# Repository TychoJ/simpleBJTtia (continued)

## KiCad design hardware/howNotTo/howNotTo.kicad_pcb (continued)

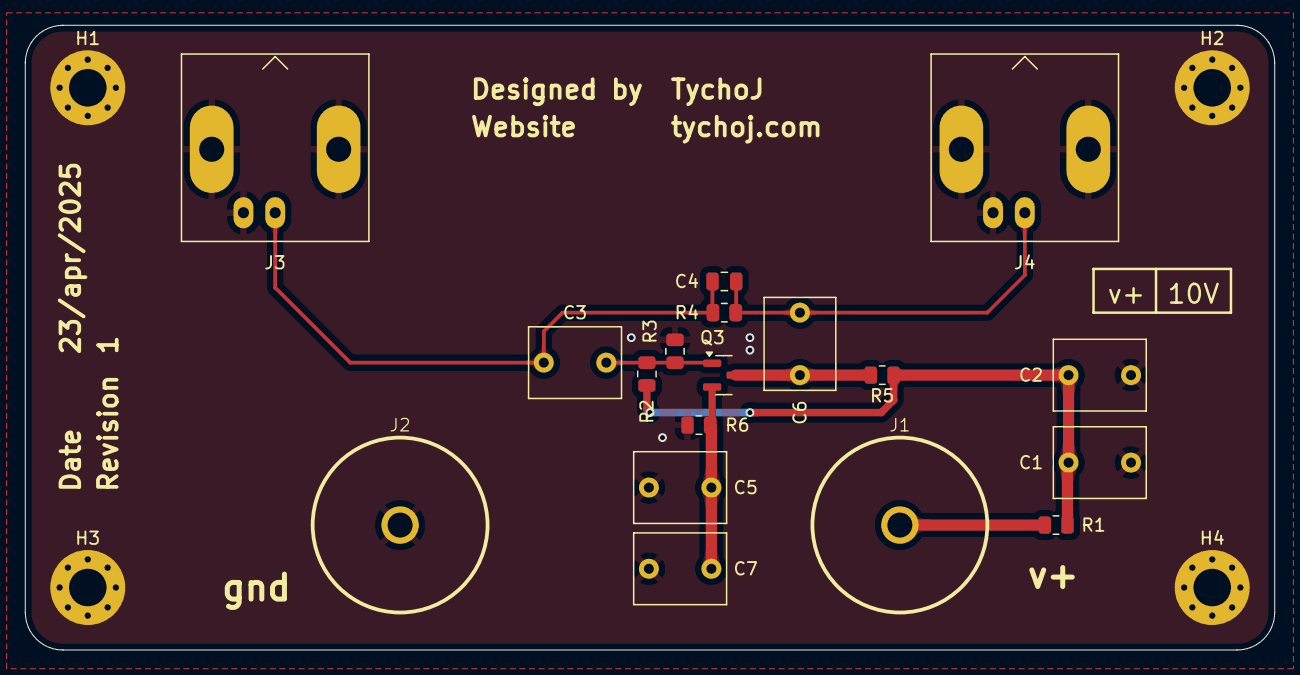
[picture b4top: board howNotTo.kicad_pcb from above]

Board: 2 copper layers, 100.0 x 50.0 mm, 22 parts (0 on the bottom side), 8 nets.

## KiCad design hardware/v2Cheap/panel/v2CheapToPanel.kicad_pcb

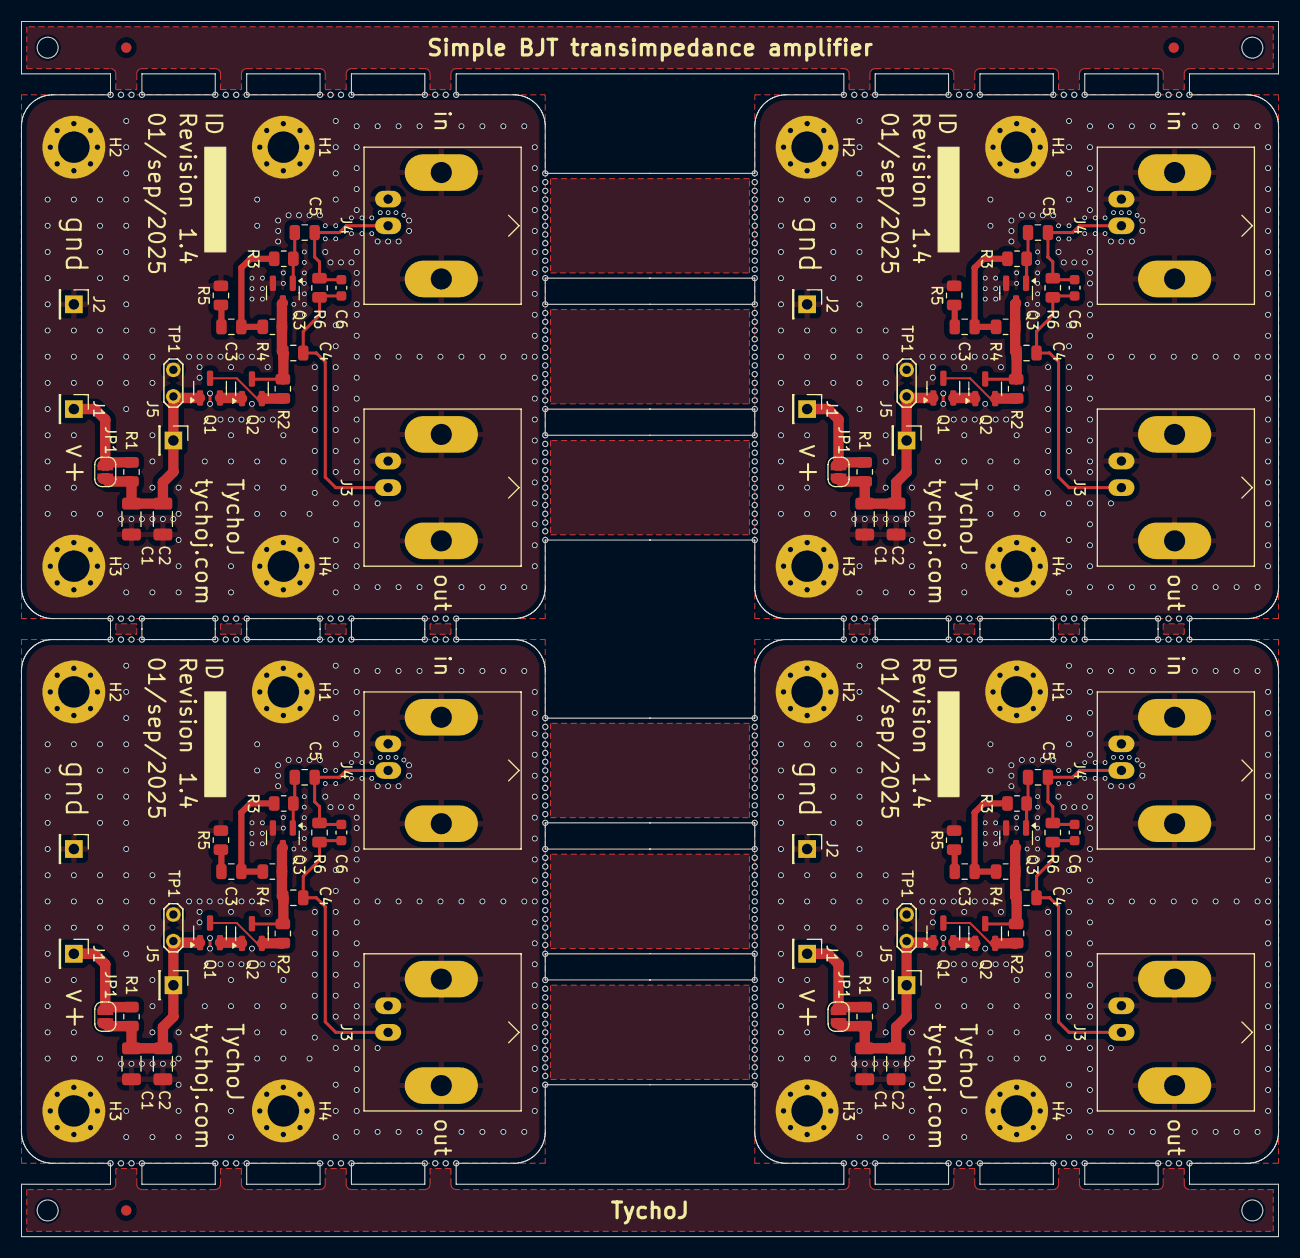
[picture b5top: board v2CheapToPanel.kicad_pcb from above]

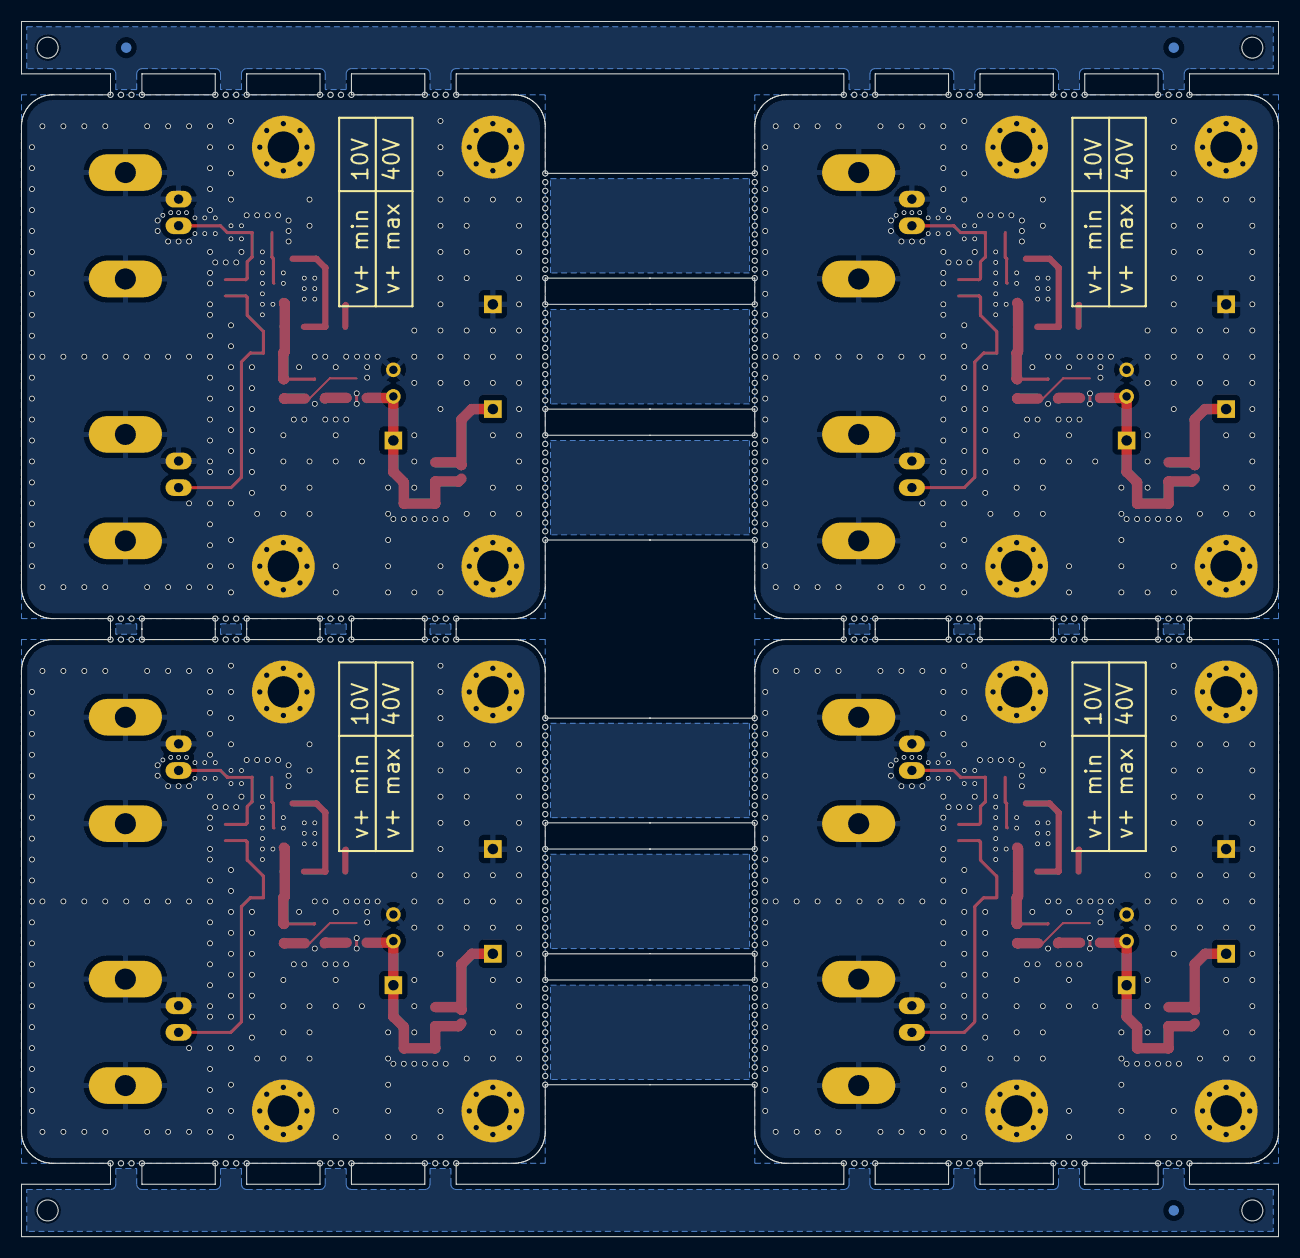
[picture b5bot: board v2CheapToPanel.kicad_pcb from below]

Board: 2 copper layers, 120.0 x 116.0 mm, 398 parts (3 on the bottom side), 44 nets.

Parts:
C1, C1#2, C1#3, C1#4, C2, C2#2, C2#3, C2#4: 4u7; C_1206_3216Metric
C3, C3#2, C3#3, C3#4: 10n; C_0805_2012Metric
C4, C4#2, C4#3, C4#4, C5, C5#2, C5#3, C5#4: 1u; C_0805_2012Metric
C6, C6#2, C6#3, C6#4: TBD; C_0603_1608Metric
H1, H1#2, H1#3, H1#4, H2, H2#2, H2#3, H2#4, H3, H3#2, H3#3, H3#4, H4, H4#2, H4#3, H4#4: MountingHole_Pad_MP; MountingHole_3mm_Pad_Via
J1, J1#2, J1#3, J1#4: +10V; PinHeader_1x01_P2.54mm_Vertical
J2, J2#2, J2#3, J2#4: GND; PinHeader_1x01_P2.54mm_Vertical
J3, J3#2, J3#3, J3#4, J4, J4#2, J4#3, J4#4: Conn_Coaxial; BNC_Amphenol_B6252HB-NPP3G-50_Horizontal
J5, J5#2, J5#3, J5#4: Conn_01x01_Pin; PinHeader_1x01_P2.54mm_Vertical
JP1, JP1#2, JP1#3, JP1#4: SolderJumper_2_Open; SolderJumper-2_P1.3mm_Open_RoundedPad1.0x1.5mm
KiKit_FID_B_1, KiKit_FID_B_2, KiKit_FID_B_3: Fiducial
KiKit_FID_T_1, KiKit_FID_T_2, KiKit_FID_T_3: Fiducial
KiKit_MB_1_1, KiKit_MB_1_2, KiKit_MB_1_3, KiKit_MB_1_4, KiKit_MB_1_5, KiKit_MB_1_6, KiKit_MB_1_7, KiKit_MB_1_8, KiKit_MB_1_9, KiKit_MB_1_10, KiKit_MB_1_11, KiKit_MB_1_12, KiKit_MB_1_13, KiKit_MB_2_1, KiKit_MB_2_2, KiKit_MB_2_3, KiKit_MB_2_4, KiKit_MB_2_5, KiKit_MB_2_6, KiKit_MB_2_7, KiKit_MB_2_8, KiKit_MB_2_9, KiKit_MB_2_10, KiKit_MB_2_11, KiKit_MB_2_12, KiKit_MB_2_13, KiKit_MB_3_1, KiKit_MB_3_2, KiKit_MB_3_3, KiKit_MB_3_4, KiKit_MB_3_5, KiKit_MB_3_6, KiKit_MB_3_7, KiKit_MB_3_8, KiKit_MB_3_9, KiKit_MB_3_10, KiKit_MB_3_11, KiKit_MB_3_12, KiKit_MB_3_13, KiKit_MB_4_1, KiKit_MB_4_2, KiKit_MB_4_3, KiKit_MB_4_4, KiKit_MB_5_1, KiKit_MB_5_2, KiKit_MB_5_3, KiKit_MB_5_4, KiKit_MB_6_1, KiKit_MB_6_2, KiKit_MB_6_3, KiKit_MB_6_4, KiKit_MB_7_1, KiKit_MB_7_2, KiKit_MB_7_3, KiKit_MB_7_4, KiKit_MB_8_1, KiKit_MB_8_2, KiKit_MB_8_3, KiKit_MB_8_4, KiKit_MB_9_1, KiKit_MB_9_2, KiKit_MB_9_3, KiKit_MB_9_4, KiKit_MB_10_1, KiKit_MB_10_2, KiKit_MB_10_3, KiKit_MB_10_4, KiKit_MB_11_1, KiKit_MB_11_2, KiKit_MB_11_3, KiKit_MB_11_4, KiKit_MB_12_1, KiKit_MB_12_2, KiKit_MB_12_3, KiKit_MB_12_4, KiKit_MB_12_5, KiKit_MB_12_6, KiKit_MB_12_7, KiKit_MB_12_8, KiKit_MB_12_9, KiKit_MB_12_10, KiKit_MB_12_11, KiKit_MB_12_12, KiKit_MB_12_13, KiKit_MB_13_1, KiKit_MB_13_2, KiKit_MB_13_3, KiKit_MB_13_4, KiKit_MB_13_5, KiKit_MB_13_6, KiKit_MB_13_7, KiKit_MB_13_8, KiKit_MB_13_9, KiKit_MB_13_10, KiKit_MB_13_11, KiKit_MB_13_12, KiKit_MB_13_13, KiKit_MB_14_1, KiKit_MB_14_2, KiKit_MB_14_3, KiKit_MB_14_4, KiKit_MB_14_5, KiKit_MB_14_6, KiKit_MB_14_7, KiKit_MB_14_8, KiKit_MB_14_9, KiKit_MB_14_10, KiKit_MB_14_11, KiKit_MB_14_12, KiKit_MB_14_13, KiKit_MB_15_1, KiKit_MB_15_2, KiKit_MB_15_3, KiKit_MB_15_4, KiKit_MB_16_1, KiKit_MB_16_2, KiKit_MB_16_3, KiKit_MB_16_4, KiKit_MB_17_1, KiKit_MB_17_2, KiKit_MB_17_3, KiKit_MB_17_4, KiKit_MB_18_1, KiKit_MB_18_2, KiKit_MB_18_3, KiKit_MB_18_4, KiKit_MB_19_1, KiKit_MB_19_2, KiKit_MB_19_3, KiKit_MB_19_4, KiKit_MB_20_1, KiKit_MB_20_2, KiKit_MB_20_3, KiKit_MB_20_4, KiKit_MB_21_1, KiKit_MB_21_2, KiKit_MB_21_3, KiKit_MB_21_4, KiKit_MB_22_1, KiKit_MB_22_2, KiKit_MB_22_3, KiKit_MB_22_4, KiKit_MB_23_1, KiKit_MB_23_2, KiKit_MB_23_3, KiKit_MB_23_4, KiKit_MB_23_5, KiKit_MB_23_6, KiKit_MB_23_7, KiKit_MB_23_8, KiKit_MB_23_9, KiKit_MB_23_10, KiKit_MB_23_11, KiKit_MB_23_12, KiKit_MB_23_13, KiKit_MB_24_1, KiKit_MB_24_2, KiKit_MB_24_3, KiKit_MB_24_4, KiKit_MB_24_5, KiKit_MB_24_6, KiKit_MB_24_7, KiKit_MB_24_8, KiKit_MB_24_9, KiKit_MB_24_10, KiKit_MB_24_11, KiKit_MB_24_12, KiKit_MB_24_13, KiKit_MB_25_1, KiKit_MB_25_2, KiKit_MB_25_3, KiKit_MB_25_4, KiKit_MB_25_5, KiKit_MB_25_6, KiKit_MB_25_7, KiKit_MB_25_8, KiKit_MB_25_9, KiKit_MB_25_10, KiKit_MB_25_11, KiKit_MB_25_12, KiKit_MB_25_13, KiKit_MB_26_1, KiKit_MB_26_2, KiKit_MB_26_3, KiKit_MB_26_4, KiKit_MB_27_1, KiKit_MB_27_2, KiKit_MB_27_3, KiKit_MB_27_4, KiKit_MB_28_1, KiKit_MB_28_2, KiKit_MB_28_3, KiKit_MB_28_4, KiKit_MB_29_1, KiKit_MB_29_2, KiKit_MB_29_3, KiKit_MB_29_4, KiKit_MB_30_1, KiKit_MB_30_2, KiKit_MB_30_3, KiKit_MB_30_4, KiKit_MB_31_1, KiKit_MB_31_2, KiKit_MB_31_3, KiKit_MB_31_4, KiKit_MB_32_1, KiKit_MB_32_2, KiKit_MB_32_3, KiKit_MB_32_4, KiKit_MB_33_1, KiKit_MB_33_2, KiKit_MB_33_3, KiKit_MB_33_4, KiKit_MB_34_1, KiKit_MB_34_2, KiKit_MB_34_3, KiKit_MB_34_4, KiKit_MB_34_5, KiKit_MB_34_6, KiKit_MB_34_7, KiKit_MB_34_8, KiKit_MB_34_9, KiKit_MB_34_10, KiKit_MB_34_11, KiKit_MB_34_12, KiKit_MB_34_13, KiKit_MB_35_1, KiKit_MB_35_2, KiKit_MB_35_3, KiKit_MB_35_4, KiKit_MB_35_5, KiKit_MB_35_6, KiKit_MB_35_7, KiKit_MB_35_8, KiKit_MB_35_9, KiKit_MB_35_10, KiKit_MB_35_11, KiKit_MB_35_12, KiKit_MB_35_13, KiKit_MB_36_1, KiKit_MB_36_2, KiKit_MB_36_3, KiKit_MB_36_4, KiKit_MB_36_5, KiKit_MB_36_6, KiKit_MB_36_7, KiKit_MB_36_8, KiKit_MB_36_9, KiKit_MB_36_10, KiKit_MB_36_11, KiKit_MB_36_12, KiKit_MB_36_13, KiKit_MB_37_1, KiKit_MB_37_2, KiKit_MB_37_3, KiKit_MB_37_4, KiKit_MB_38_1, KiKit_MB_38_2, KiKit_MB_38_3, KiKit_MB_38_4, KiKit_MB_39_1, KiKit_MB_39_2, KiKit_MB_39_3, KiKit_MB_39_4, KiKit_MB_40_1, KiKit_MB_40_2, KiKit_MB_40_3, KiKit_MB_40_4, KiKit_MB_41_1, KiKit_MB_41_2, KiKit_MB_41_3, KiKit_MB_41_4, KiKit_MB_42_1, KiKit_MB_42_2, KiKit_MB_42_3, KiKit_MB_42_4, KiKit_MB_43_1, KiKit_MB_43_2, KiKit_MB_43_3, KiKit_MB_43_4, KiKit_MB_44_1, KiKit_MB_44_2, KiKit_MB_44_3, KiKit_MB_44_4: NPTH
KiKit_TO_1, KiKit_TO_2, KiKit_TO_3, KiKit_TO_4: NPTH
Q1, Q1#2, Q1#3, Q1#4, Q2, Q2#2, Q2#3, Q2#4: MMBFJ112; SOT-23
Q3, Q3#2, Q3#3, Q3#4: 2PD601ARL,215; SOT-23
R1, R1#2, R1#3, R1#4: 100; R_0805_2012Metric
R2, R2#2, R2#3, R2#4: 1k; R_0805_2012Metric
R3, R3#2, R3#3, R3#4: 470k; R_0805_2012Metric
R4, R4#2, R4#3, R4#4: 1Meg; R_0805_2012Metric
R5, R5#2, R5#3, R5#4, R6, R6#2, R6#3, R6#4: 100k; R_0805_2012Metric
TP1, TP1#2, TP1#3, TP1#4: TestPoint_2Pole; TestPoint_2Pads_Pitch2.54mm_Drill0.8mm

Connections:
Board_0-GND: C1#4.1, C2#4.1, H1.1 (MP), H2#2.1 (MP), H3#4.1 (MP), H4.1 (MP), J2.1, J3#4.2 (Ext), J4#3.2 (Ext), Q3#2.2 (E), R5#4.2, TP1#4.1
Board_0-Net-(C3-Pad1): C3#4.1, R3#3.2, R4#2.1
Board_0-Net-(C3-Pad2): C3#4.2, R5#4.1
Board_0-Net-(J1-Pin_1): J1#3.1, JP1.1 (A), R1.1
Board_0-Net-(J3-In): C4#2.1, C6.1, J3#4.1 (In), R6#3.2
Board_0-Net-(J4-In): C5#2.2, C6.2, J4#3.1 (In), R6#3.1
Board_0-Net-(J5-Pin_1): C1#4.2, C2#4.2, J5#4.1, JP1.2 (B), Q1.1 (D), R1.2, TP1#4.2
Board_0-Net-(Q1-G): Q1.3 (G), Q2#4.2 (S), R2.1
Board_0-Net-(Q1-S): Q1.2 (S), Q2#4.1 (D)
Board_0-Net-(Q2-G): C4#2.2, Q2#4.3 (G), Q3#2.3 (C), R2.2, R4#2.2
Board_0-Net-(Q3-B): C5#2.1, Q3#2.1 (B), R3#3.1
Board_1-GND: C1#2.1, C2.1, H1#3.1 (MP), H2#4.1 (MP), H3.1 (MP), H4#3.1 (MP), J2#2.1, J3#2.2 (Ext), J4#4.2 (Ext), Q3#3.2 (E), R5#2.2, TP1#3.1
Board_1-Net-(C3-Pad1): C3.1, R3#2.2, R4.1
Board_1-Net-(C3-Pad2): C3.2, R5#2.1
Board_1-Net-(J1-Pin_1): J1.1, JP1#2.1 (A), R1#3.1
Board_1-Net-(J3-In): C4#3.1, C6#3.1, J3#2.1 (In), R6.2
Board_1-Net-(J4-In): C5.2, C6#3.2, J4#4.1 (In), R6.1
Board_1-Net-(J5-Pin_1): C1#2.2, C2.2, J5#3.1, JP1#2.2 (B), Q1#2.1 (D), R1#3.2, TP1#3.2
Board_1-Net-(Q1-G): Q1#2.3 (G), Q2#3.2 (S), R2#2.1
Board_1-Net-(Q1-S): Q1#2.2 (S), Q2#3.1 (D)
Board_1-Net-(Q2-G): C4#3.2, Q2#3.3 (G), Q3#3.3 (C), R2#2.2, R4.2
Board_1-Net-(Q3-B): C5.1, Q3#3.1 (B), R3#2.1
Board_2-GND: C1#3.1, C2#2.1, H1#4.1 (MP), H2.1 (MP), H3#2.1 (MP), H4#2.1 (MP), J2#3.1, J3#3.2 (Ext), J4.2 (Ext), Q3#4.2 (E), R5.2, TP1.1
Board_2-Net-(C3-Pad1): C3#3.1, R3#4.2, R4#3.1
Board_2-Net-(C3-Pad2): C3#3.2, R5.1
Board_2-Net-(J1-Pin_1): J1#4.1, JP1#3.1 (A), R1#2.1
Board_2-Net-(J3-In): C4.1, C6#4.1, J3#3.1 (In), R6#2.2
Board_2-Net-(J4-In): C5#4.2, C6#4.2, J4.1 (In), R6#2.1
Board_2-Net-(J5-Pin_1): C1#3.2, C2#2.2, J5.1, JP1#3.2 (B), Q1#4.1 (D), R1#2.2, TP1.2
Board_2-Net-(Q1-G): Q1#4.3 (G), Q2.2 (S), R2#4.1
Board_2-Net-(Q1-S): Q1#4.2 (S), Q2.1 (D)
Board_2-Net-(Q2-G): C4.2, Q2.3 (G), Q3#4.3 (C), R2#4.2, R4#3.2
Board_2-Net-(Q3-B): C5#4.1, Q3#4.1 (B), R3#4.1
Board_3-GND: C1.1, C2#3.1, H1#2.1 (MP), H2#3.1 (MP), H3#3.1 (MP), H4#4.1 (MP), J2#4.1, J3.2 (Ext), J4#2.2 (Ext), Q3.2 (E), R5#3.2, TP1#2.1
Board_3-Net-(C3-Pad1): C3#2.1, R3.2, R4#4.1
Board_3-Net-(C3-Pad2): C3#2.2, R5#3.1
Board_3-Net-(J1-Pin_1): J1#2.1, JP1#4.1 (A), R1#4.1
Board_3-Net-(J3-In): C4#4.1, C6#2.1, J3.1 (In), R6#4.2
Board_3-Net-(J4-In): C5#3.2, C6#2.2, J4#2.1 (In), R6#4.1
Board_3-Net-(J5-Pin_1): C1.2, C2#3.2, J5#2.1, JP1#4.2 (B), Q1#3.1 (D), R1#4.2, TP1#2.2
Board_3-Net-(Q1-G): Q1#3.3 (G), Q2#2.2 (S), R2#3.1
Board_3-Net-(Q1-S): Q1#3.2 (S), Q2#2.1 (D)
Board_3-Net-(Q2-G): C4#4.2, Q2#2.3 (G), Q3.3 (C), R2#3.2, R4#4.2
Board_3-Net-(Q3-B): C5#3.1, Q3.1 (B), R3.1

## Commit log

2025-02-16 adding hardware revision v1.2
2025-02-16 adding simulations for hardware revision v1.2
2025-02-16 adding simulations for hardware revision v2.0
2025-02-16 Keep generated files from LTspice out of the repository
2025-02-16 Place hardware revision 1 in its own folder
2025-02-16 3d models of connectors
2025-02-16 Move 3d models to hardware version folder
2025-02-16 Add power connector footprints
2025-02-16 Use project power pin footprints
2025-02-16 Make the simulation circuit the same as the pcb circuit
2025-04-18 Update project to kicad V9
2025-07-02 Add simulations
2025-07-02 update V2 design
2025-07-02 Update .gitignore for dfm kicad plugin
2025-07-02 Create how not to kicad design
2025-07-02 An update
2025-12-06 update v2
2025-12-06 update the how not to design
2025-12-06 Add crosstalk simulations
2025-12-06 Add symbol library
2025-12-06 Start V4 design
2025-12-06 Add panel for the V2 cheap design
2025-12-06 Keep gerbers out of the repo
2025-12-06 Setup for an input generation module
2025-12-06 Add footprints
2025-12-06 Add a cheap version of the v2 design
2025-12-06 Update gitignore to keep gerbers out of the repo
2026-01-18 Adding initial v4 design
